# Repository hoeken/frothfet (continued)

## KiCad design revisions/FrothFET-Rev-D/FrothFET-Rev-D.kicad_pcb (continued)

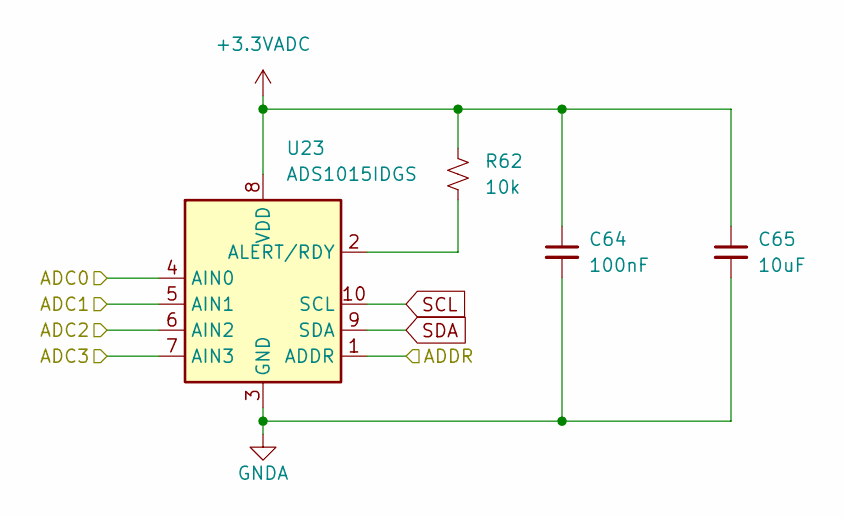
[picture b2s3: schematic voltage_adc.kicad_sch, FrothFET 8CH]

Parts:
C64: 100nF; C_0805_2012Metric_Pad1.18x1.45mm_HandSolder; LCSC C49678
C65: 10uF; C_0805_2012Metric_Pad1.18x1.45mm_HandSolder; LCSC C1952580
R62: 10k; R_0805_2012Metric_Pad1.20x1.40mm_HandSolder; LCSC C84376
U23: ADS1015IDGS; TSSOP-10_3x3mm_P0.5mm; LCSC C193969

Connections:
+3.3VADC: C64.1, C65.1, R62.2, U23.8 (VDD); also elsewhere on the board
GND: C64.2, C65.2, U23.1 (ADDR), U23.3 (GND); also elsewhere on the board
unnamed: R62.1, U23.2 (ALERT/RDY)
SCL: U23.10 (SCL); also elsewhere on the board
SDA: U23.9 (SDA); also elsewhere on the board
VOLT5: U23.4 (AIN0); also elsewhere on the board
VOLT6: U23.5 (AIN1); also elsewhere on the board
VOLT7: U23.6 (AIN2); also elsewhere on the board
VOLT8: U23.7 (AIN3); also elsewhere on the board

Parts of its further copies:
C62: 100nF; C_0805_2012Metric_Pad1.18x1.45mm_HandSolder; LCSC C49678
C63: 10uF; C_0805_2012Metric_Pad1.18x1.45mm_HandSolder; LCSC C1952580
R61: 10k; R_0805_2012Metric_Pad1.20x1.40mm_HandSolder; LCSC C84376
U22: ADS1015IDGS; TSSOP-10_3x3mm_P0.5mm; LCSC C193969

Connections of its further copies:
+3.3VADC: C62.1, C63.1, R61.2, U22.1 (ADDR), U22.8 (VDD); also elsewhere on the board
GND: C62.2, C63.2, U22.3 (GND); also elsewhere on the board
unnamed: R61.1, U22.2 (ALERT/RDY)
SCL: U22.10 (SCL); also elsewhere on the board
SDA: U22.9 (SDA); also elsewhere on the board
VOLT1: U22.4 (AIN0); also elsewhere on the board
VOLT2: U22.5 (AIN1); also elsewhere on the board
VOLT3: U22.6 (AIN2); also elsewhere on the board
VOLT4: U22.7 (AIN3); also elsewhere on the board

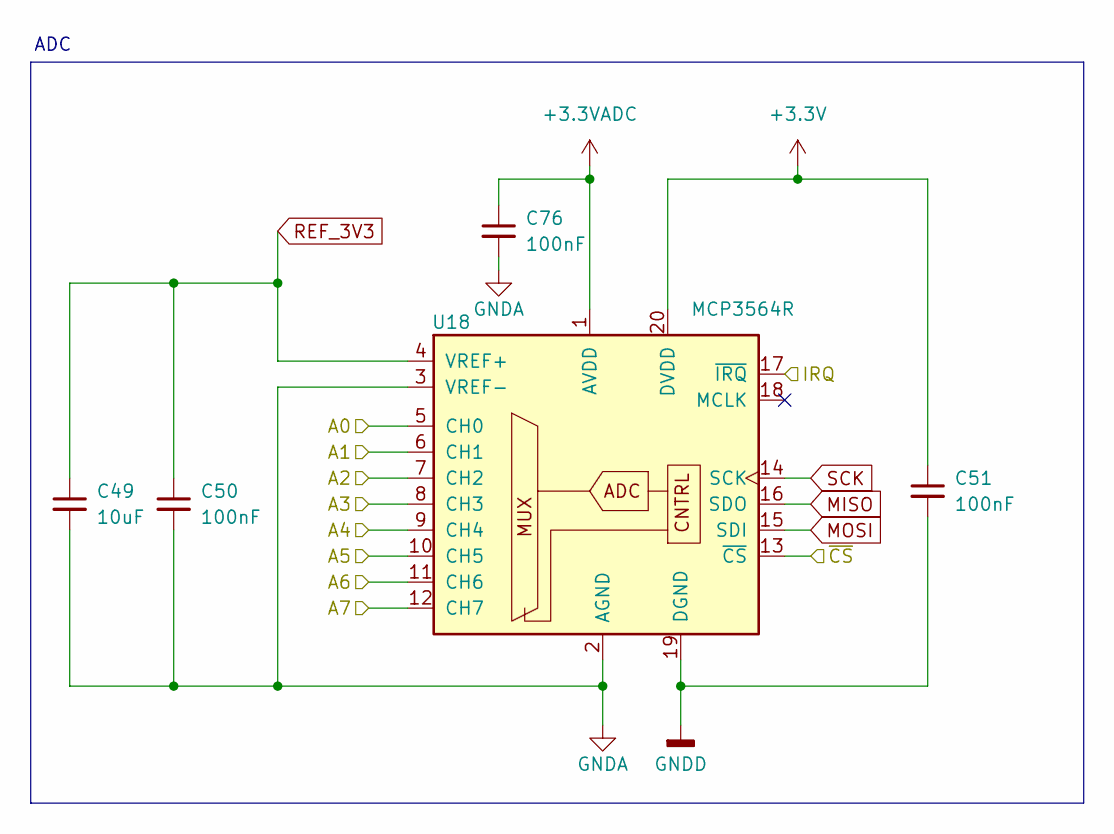
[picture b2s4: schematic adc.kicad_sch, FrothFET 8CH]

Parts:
C49: 10uF; C_0805_2012Metric_Pad1.18x1.45mm_HandSolder; LCSC C1952580
C50, C51, C76: 100nF; C_0805_2012Metric_Pad1.18x1.45mm_HandSolder; LCSC C49678
U18: MCP3564R; TSSOP-20_4.4x6.5mm_P0.65mm; Mouser 579-MCP3564R-E/ST

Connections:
+3.3V: C51.1, U18.20 (DVDD); also elsewhere on the board
+3.3VADC: C76.1, U18.1 (AVDD); also elsewhere on the board
/CHANNEL 1/CURRENT_ADC: U18.5 (CH0); also elsewhere on the board
/CHANNEL 2/CURRENT_ADC: U18.6 (CH1); also elsewhere on the board
/CHANNEL 3/CURRENT_ADC: U18.7 (CH2); also elsewhere on the board
/CHANNEL 4/CURRENT_ADC: U18.8 (CH3); also elsewhere on the board
/CHANNEL 5/CURRENT_ADC: U18.9 (CH4); also elsewhere on the board
/CHANNEL 6/CURRENT_ADC: U18.10 (CH5); also elsewhere on the board
/CHANNEL 7/CURRENT_ADC: U18.11 (CH6); also elsewhere on the board
/CHANNEL 8/CURRENT_ADC: U18.12 (CH7); also elsewhere on the board
/HIRES ADC1/IRQ: U18.17 (~IRQ); also elsewhere on the board
ADC1_CS: U18.13 (~CS); also elsewhere on the board
GND: C49.2, C50.2, C51.2, C76.2, U18.2 (AGND), U18.3 (VREF-), U18.19 (DGND); also elsewhere on the board
MISO: U18.16 (SDO); also elsewhere on the board
MOSI: U18.15 (SDI); also elsewhere on the board
REF_3V3: C49.1, C50.1, U18.4 (VREF+); also elsewhere on the board
SCK: U18.14 (SCK); also elsewhere on the board

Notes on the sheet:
ADC

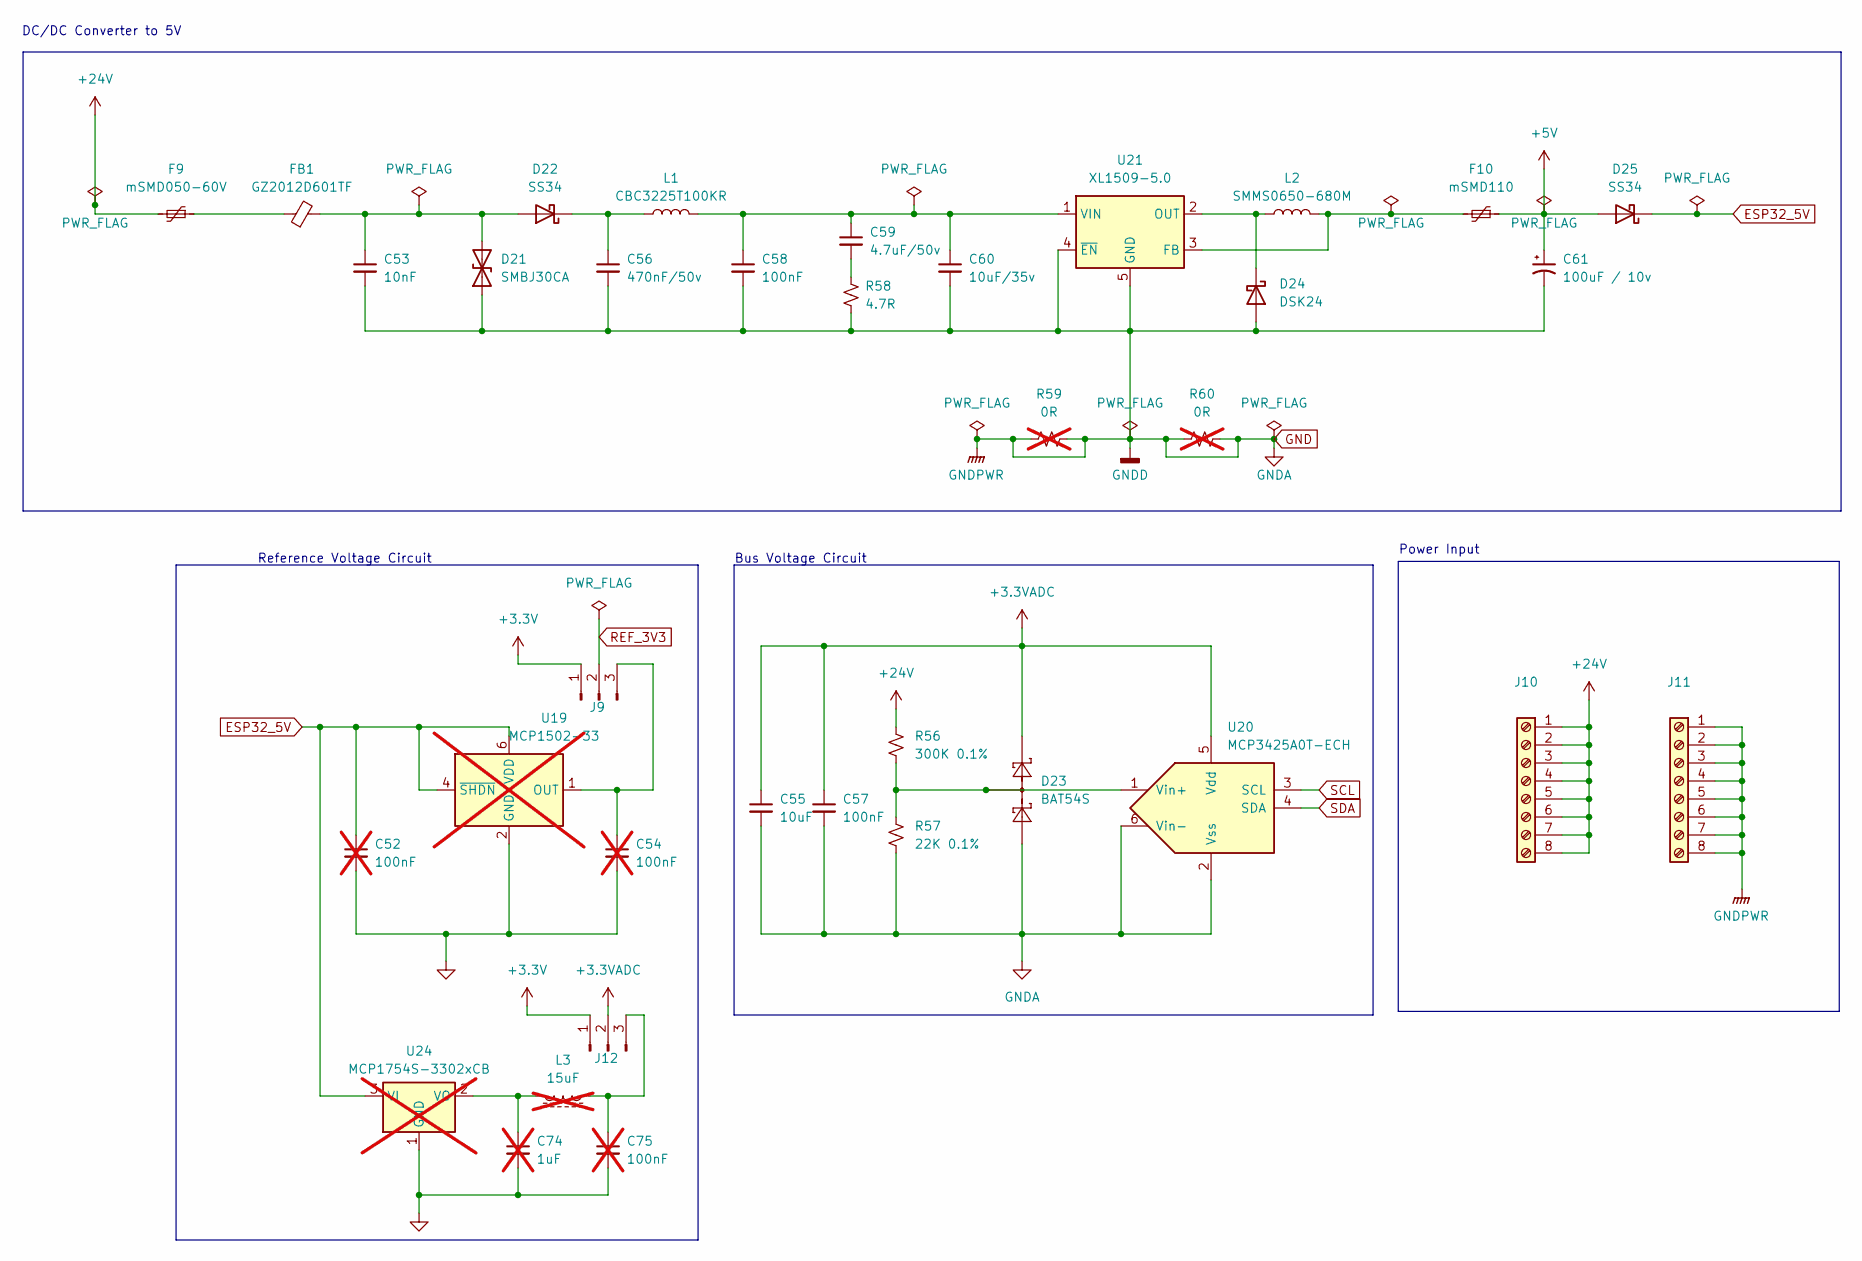
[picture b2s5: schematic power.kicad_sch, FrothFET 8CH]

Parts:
C52, C54, C75: 100nF; C_0805_2012Metric_Pad1.18x1.45mm_HandSolder; LCSC C49678; not fitted
C53: 10nF; C_0805_2012Metric_Pad1.18x1.45mm_HandSolder; LCSC C83170
C55: 10uF; C_0805_2012Metric_Pad1.18x1.45mm_HandSolder; LCSC C1952580
C56: 470nF/50v; C_0805_2012Metric_Pad1.18x1.45mm_HandSolder; LCSC C106843
C57, C58: 100nF; C_0805_2012Metric_Pad1.18x1.45mm_HandSolder; LCSC C49678
C59: 4.7uF/50v; C_0805_2012Metric_Pad1.18x1.45mm_HandSolder; LCSC C2991173
C60: 10uF/35v; C_1206_3216Metric_Pad1.33x1.80mm_HandSolder; LCSC C454102
C61: 100uF / 10v; CP_EIA-3528-21_Kemet-B; LCSC C90975
C74: 1uF; C_0805_2012Metric_Pad1.18x1.45mm_HandSolder; LCSC C519973; not fitted
D21: SMBJ30CA; D_SMB; LCSC C284101
D22, D25: SS34; D_SMA; Mouser 512-SS34
D23: BAT54S; SOT-23; LCSC C727126
D24: DSK24; D_SOD-123; Mouser 610-CMHSH5-2L
F9: mSMD050-60V; Fuse_1812_4532Metric_Pad1.30x3.40mm_HandSolder; LCSC C70113
F10: mSMD110; Fuse_1812_4532Metric_Pad1.30x3.40mm_HandSolder; LCSC C69691
FB1: GZ2012D601TF; L_0805_2012Metric; LCSC C1017
J9, J12: Conn_01x03_Pin; PinHeader_1x03_P2.54mm_Vertical
J10, J11: Screw_Terminal_01x08; Busbar Rev D
L1: CBC3225T100KR; L_1210_3225Metric; LCSC C90321
L2: SMMS0650-680M; L_Chilisin_BMRB00060650; LCSC C2894721
L3: 15uF; L_0805_2012Metric_Pad1.05x1.20mm_HandSolder; Mouser 652-CV201210-150K; not fitted
R56: 300K 0.1%; R_0805_2012Metric_Pad1.20x1.40mm_HandSolder; LCSC C865386
R57: 22K 0.1%; R_0805_2012Metric_Pad1.20x1.40mm_HandSolder; LCSC C865312
R58: 4.7R; R_0805_2012Metric_Pad1.20x1.40mm_HandSolder; LCSC C137513
R59, R60: 0R; R_0805_2012Metric_Pad1.20x1.40mm_HandSolder; not fitted
U19: MCP1502-33; SOT-23-6; Mouser 579-MCP1502T-33E/CHY; not fitted
U20: MCP3425A0T-ECH; SOT-23-6; Mouser 579-MCP3425A0T-E/CH
U21: XL1509-5.0; SOIC-8_3.9x4.9mm_P1.27mm; LCSC C2902368
U24: MCP1754S-3302xCB; SOT-23; Mouser 579-MCP1754ST3302EMB; not fitted

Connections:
+3.3V: J9.1, J12.1; also elsewhere on the board
+3.3VADC: C55.1, C57.1, D23.2 (K), J12.2, U20.5 (Vdd); also elsewhere on the board
+5V: C61.1, D25.2 (A), F10.1; also elsewhere on the board
+24V: F9.2, J10.1, J10.2, J10.3, J10.4, J10.5, J10.6, J10.7, J10.8, R56.2; also elsewhere on the board
ESP32_5V: C52.1, D25.1 (K), U19.4 (~SHDN), U19.6 (VDD), U24.3 (VI); also elsewhere on the board
GND: C52.2, C53.2, C54.2, C55.2, C56.2, C57.2, C58.2, C60.2, C61.2, C74.2, C75.2, D21.1 (A1), D23.1 (A), D24.2 (A), J11.1, J11.2, J11.3, J11.4, J11.5, J11.6, J11.7, J11.8, R57.1, R58.2, R59.1, R59.2, R60.1, R60.2, U19.2 (GND), U19.3 (GND), U19.5 (GND), U20.2 (Vss), U20.6 (Vin-), U21.4 (~EN), U21.5 (GND), U21.6 (GND), U21.7 (GND), U21.8 (GND), U24.1 (GND); also elsewhere on the board
unnamed: C59.2, R58.1
unnamed: C53.1, D21.2 (A2), D22.2 (A), FB1.2
unnamed: C56.1, D22.1 (K), L1.1
unnamed: D23.3 (COM), R56.1, R57.2, U20.1 (Vin+)
unnamed: D24.1 (K), L2.1, U21.2 (OUT)
unnamed: F9.1, FB1.1
unnamed: C54.1, J9.3, U19.1 (OUT)
unnamed: C75.1, J12.3, L3.1
unnamed: F10.2, L2.2, U21.3 (FB)
unnamed: C58.1, C59.1, C60.1, L1.2, U21.1 (VIN)
unnamed: C74.1, L3.2, U24.2 (VO)
REF_3V3: J9.2; also elsewhere on the board
SCL: U20.3 (SCL); also elsewhere on the board
SDA: U20.4 (SDA); also elsewhere on the board

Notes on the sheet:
Reference Voltage Circuit
DC/DC Converter to 5V
Power Input
Bus Voltage Circuit

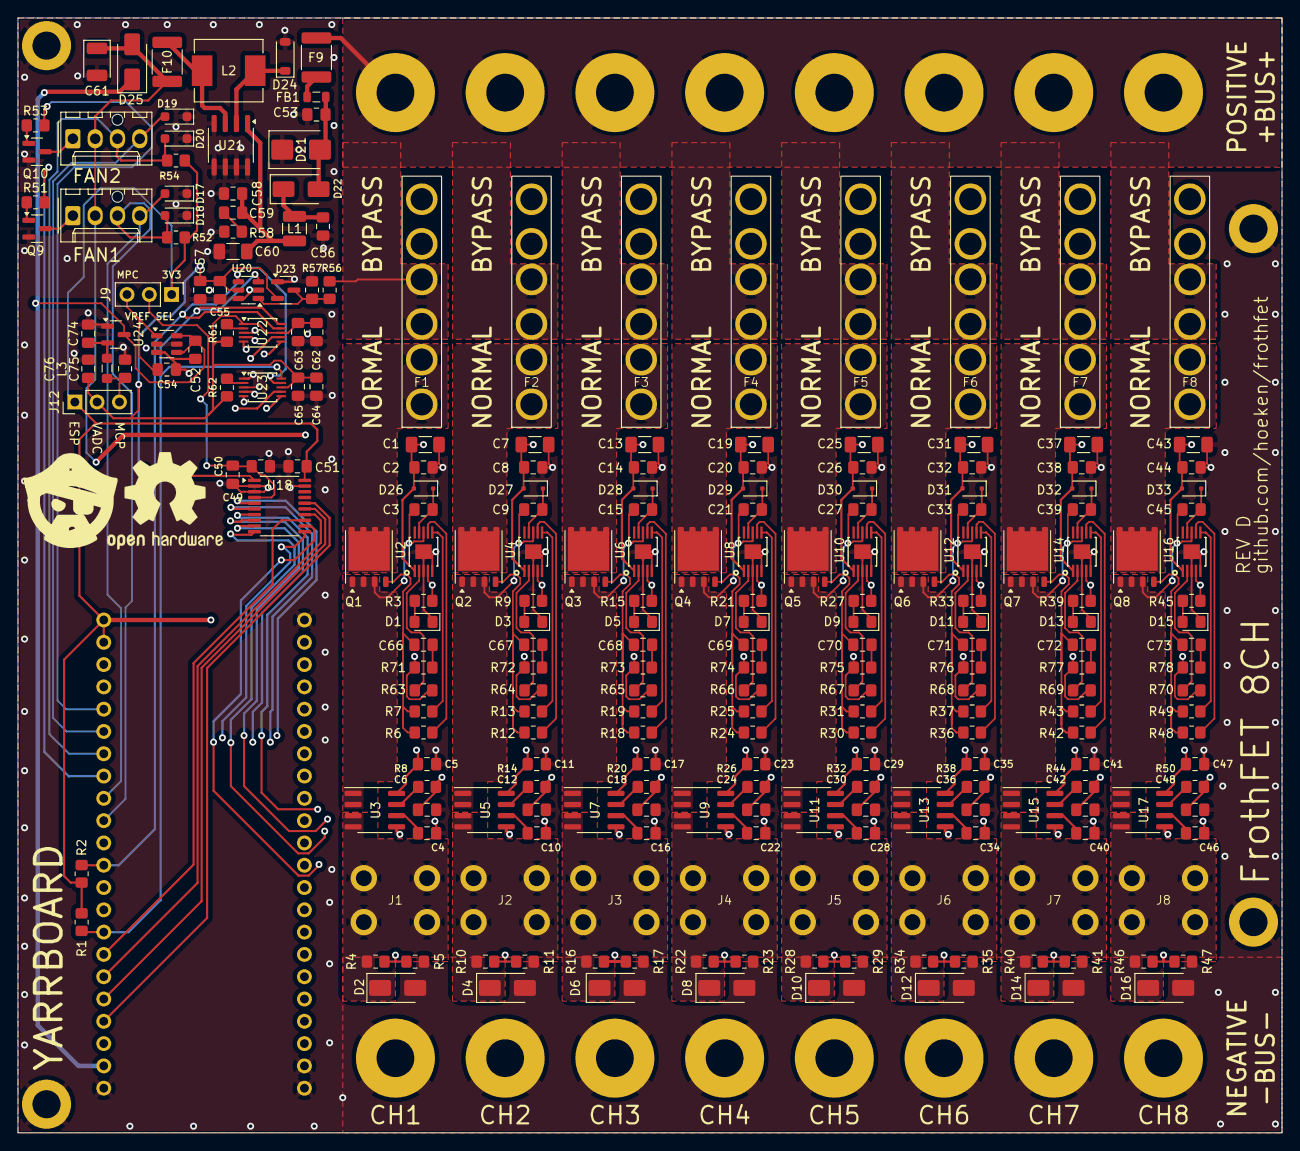
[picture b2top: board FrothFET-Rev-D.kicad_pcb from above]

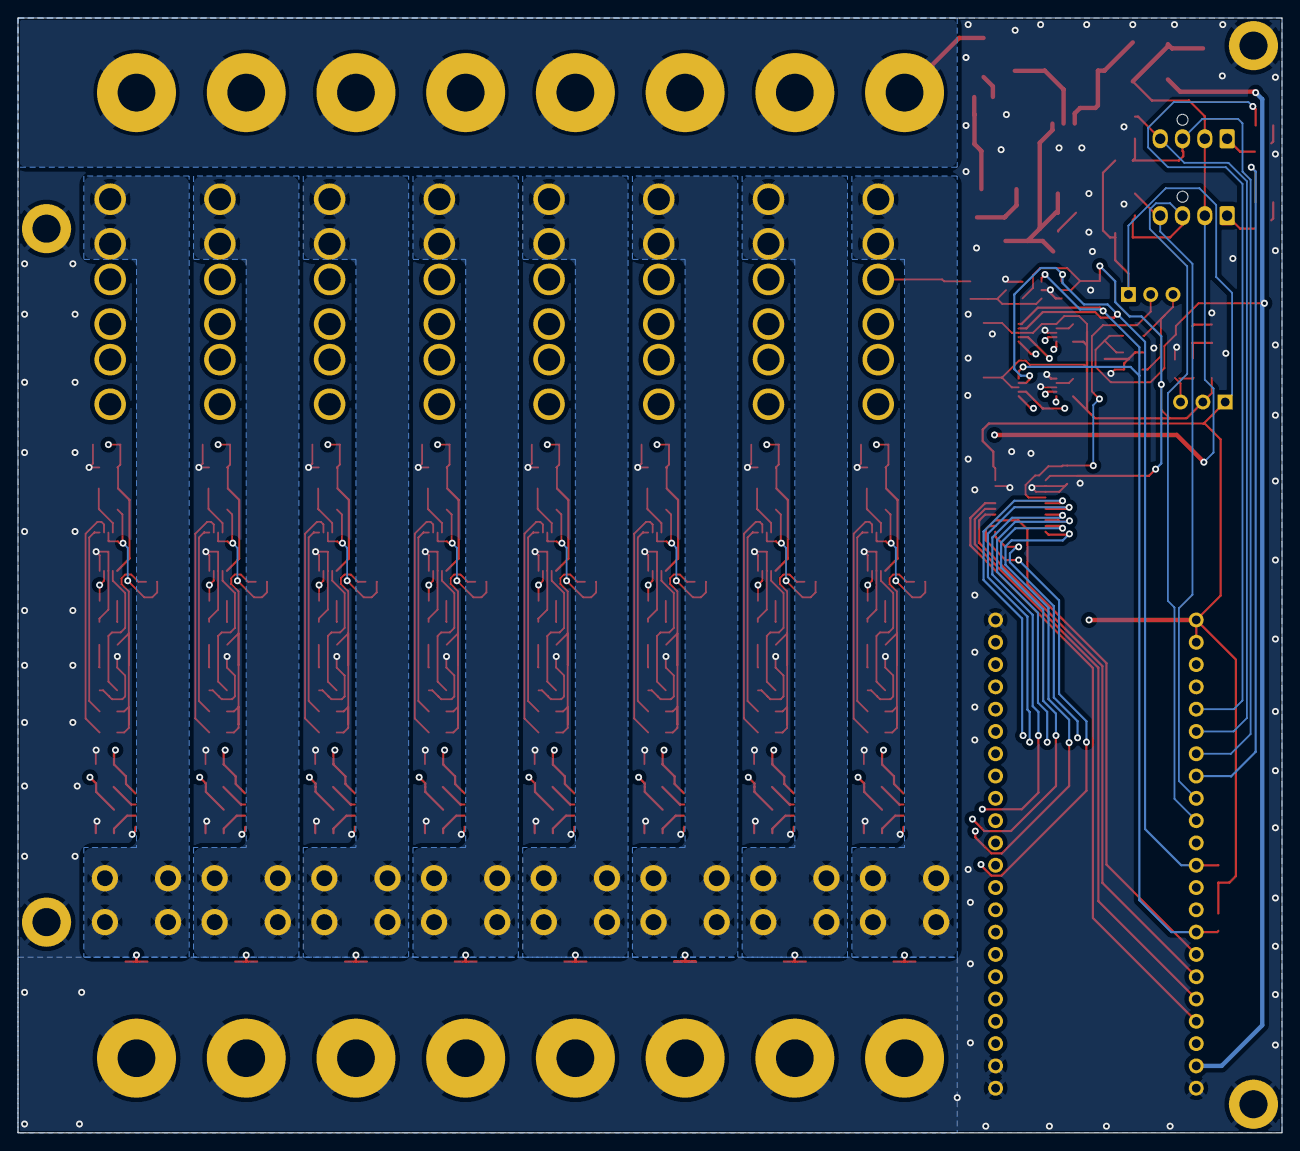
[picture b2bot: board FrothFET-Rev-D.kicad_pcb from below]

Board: 4 copper layers, 144.0 x 127.0 mm, 251 parts (2 on the bottom side), 157 nets.

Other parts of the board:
D17, D18, D19, D20: PESD3V3L1BA; D_SOD-323_HandSoldering
FAN1, FAN2: Fan_4pin; Molex 0470531000
Q9, Q10: 2N7002; SOT-23
R51, R52, R53, R54: 1k; R_0805_2012Metric_Pad1.20x1.40mm_HandSolder

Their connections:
+3.3V: R52.2, R54.2; also elsewhere on the board
+5V: FAN1.2 (+), FAN2.2 (+); also elsewhere on the board
FAN_MOSFET1: R51.2; also elsewhere on the board
FAN_MOSFET2: R53.2; also elsewhere on the board
FAN_PWM1: D17.2 (A2), FAN1.4 (PWM); also elsewhere on the board
FAN_PWM2: D19.2 (A2), FAN2.4 (PWM); also elsewhere on the board
FAN_TACH1: D18.2 (A2), FAN1.3 (Tacho), R52.1; also elsewhere on the board
FAN_TACH2: D20.2 (A2), FAN2.3 (Tacho), R54.1; also elsewhere on the board
GND: D17.1 (A1), D18.1 (A1), D19.1 (A1), D20.1 (A1), Q9.2 (S), Q10.2 (S); also elsewhere on the board
unnamed: FAN1.1 (-), Q9.3 (D)
unnamed: FAN2.1 (-), Q10.3 (D)
unnamed: Q9.1 (G), R51.1
unnamed: Q10.1 (G), R53.1

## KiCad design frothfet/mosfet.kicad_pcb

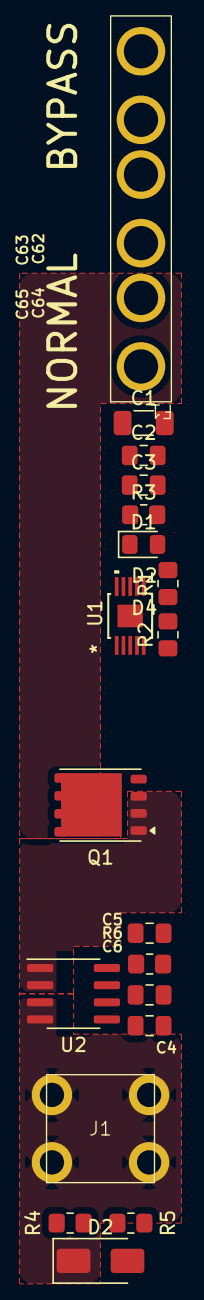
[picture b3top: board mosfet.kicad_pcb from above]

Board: 2 copper layers, 19 parts (0 on the bottom side), 17 nets, no tracks yet.

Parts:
C1: 10uF/35v; C_1206_3216Metric_Pad1.33x1.80mm_HandSolder
C2: 100nF/50v; C_0805_2012Metric_Pad1.18x1.45mm_HandSolder
C3, C5: 100nF; C_0805_2012Metric_Pad1.18x1.45mm_HandSolder
C4: 1nF; C_0805_2012Metric_Pad1.18x1.45mm_HandSolder
C6: 4.7nF; C_0805_2012Metric_Pad1.18x1.45mm_HandSolder
D1: LED; LED_0805_2012Metric_Pad1.15x1.40mm_HandSolder
D2: SS16; D_SMA
F1: ATC Fuse Bypass; ATC Bypass Fuse
J1: Conn_01x01; T44001
Q1: ISC011N06LM5ATMA1; Infineon_PG-TDSON-8_6.15x5.15mm
R1, R6: 1k; R_0805_2012Metric_Pad1.20x1.40mm_HandSolder
R2: 300K 0.1%; R_0805_2012Metric_Pad1.20x1.40mm_HandSolder
R3: 22K 0.1%; R_0805_2012Metric_Pad1.20x1.40mm_HandSolder
R4, R5: 0R; R_0805_2012Metric_Pad1.20x1.40mm_HandSolder
U1: LTC7004EMSE-PBF; MSE_10_ADI
U2: ACS725xLCTR-20AU; ACS7XX

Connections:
+3.3V: C5.1, U2.8 (VCC)
+5V: C1.1, C2.1, U1.1 (VCC)
/CURRENT_ADC: C6.1, R6.1
/PWM: R1.1, U1.4 (INP)
/VOLT_ADC: R2.1, R3.2
GNDA: C4.2, C5.2, C6.2, U2.5 (GND)
GNDPWR: C1.2, C2.2, D1.1 (K), D2.2 (A), R3.1, U1.2 (VCCUV), U1.3 (GND), U1.5 (OVLO), U1.EPAD
unnamed: D1.2 (A), R1.2
unnamed: D2.1 (K), F1.3, J1.1, R2.2, U2.3 (IP-), U2.4 (IP-)
unnamed: F1.1, Q1.1 (D)
unnamed: Q1.2 (G), R4.1, R5.1
unnamed: C3.2, Q1.3 (S), U1.8 (TS), U2.1 (IP+), U2.2 (IP+)
unnamed: C3.1, U1.9 (BST)
unnamed: R5.2, U1.6 (TGDN)
unnamed: R4.2, U1.7 (TGUP)
unnamed: C4.1, U2.6 (FILTER)
unnamed: R6.2, U2.7 (VIOUT)

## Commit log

2024-08-16 added kicad files.
2024-08-16 Update README.md
    better readme
2024-08-16 Update README.md
    psu
2024-08-16 added todo
2024-08-16 schematic looking clean.
2024-08-16 todo
2024-08-17 updated bom
2024-08-17 just need to route it...
2024-08-17 starting the mega route.
2024-08-17 fully routed
2024-08-17 clean drc
2024-08-17 erc clean
2024-08-17 just silkscreen and final review left.
2024-08-17 changed senders to screw terminals
2024-08-17 added busbar 3d model and more routing.
2024-08-17 3d model.
2024-08-17 fixed busbar resize.
2024-08-17 better esp32-s3 3d model.
2024-08-17 more 3d models.
2024-08-17 added atc fuses.
2024-08-18 more pre-production tweaks
2024-08-18 todo update
2024-08-19 added mosfet thermistor
2024-08-21 lots of big updates
2024-08-21 changed to MIC5014
2024-08-26 first pass at ltc7004
2024-10-02 renamed to frothfet.
2024-10-02 prep for new HierarchialPCB test
2024-10-02 Revert "prep for new HierarchialPCB test"
    This reverts commit 7ba467f7ba771a9ed3b62c58bdcef6315b0965ad.
2024-10-02 back to a good state
2024-10-02 first pass at new subcircuit layout
2024-10-02 resized pcb
2024-10-03 drc passing
2024-10-03 fatter power trace and layer 3 is fully ground plane now.
2024-10-04 reannotate
2024-10-04 updated a couple components, flyback diode.
2024-10-05 added selector for 3.3VADC and finalized board.
2024-10-05 Update README.md
    updated readme
2024-10-06 wrong led pn
2024-10-23 updated dnp, updatd channel voltage divider, added discharge mosfet circuit
2024-10-25 todo list and rev d testing
2024-10-25 updated voltage divider values
2024-10-25 added power leds
2024-10-25 updated the adc voltage regulator.
2024-10-25 added hole to screw connector
2024-10-25 added extra adc control lines
2024-10-25 fans are now simple on/off, cleaned up power supply drawings
2024-10-26 updated fans and also new "dump" mosfet circuit
2024-10-26 added config.
2024-10-26 added piezo buzzer
2024-10-26 updated adc and adc power supply schematics.
2024-10-29 updated todo for eventual Rev E
2024-10-29 added the up to date rev d schematic
2024-10-30 tweaks to rev d
2024-10-30 rev e channel changes.
2024-10-30 consolidated on a single adc
2024-10-31 updated the dummy load schematic.
2024-11-01 removed uvlo resistor, tied to gnd.
2024-11-01 updated todo for rev e
2024-11-01 updated pins: channel rgbs + channel 5+6 pwm pins
2024-11-01 changed to jumper resistor for voltage selection.
2024-11-01 re-calculate channel voltage divider <= 30k and 3.3v output
2024-11-01 recalculate values for adc filters - 1khz should be fine
2024-11-02 started work on rev e, looking clean at 13mm
2024-11-02 more progress on the next rev.
2024-11-02 layout of the mosfet channel passives looking good.
2024-11-02 progress - new channel layout good, zones + edges + holes fixed.
2024-11-02 changed to 0603 and various tweaks
2024-11-02 24v to fuse now on both sides.
2025-07-31 updated to kicad v9
2025-07-31 updated todo.
2025-08-15 started the process of re-layout
2025-08-16 almost ready for routing.
2025-09-10 added new esp32-s3 template and switched to lm74502 mosfet driver.
2025-09-11 updated calculations, updated esp32-s3 schematic, updated layout.
2025-09-12 worked on 3d models for all parts.
2025-09-13 worked on the bom and footprint placement
2025-09-27 changed the adc voltage regulator and vref to more common parts.
2025-09-28 lots of work on the analog system
2025-09-30 moved back to a single ground plane
2025-10-01 cant remember
2025-10-02 imported latest esp32-s3 module
2025-10-02 piezo resistor
2025-10-04 about 50% routed
2025-10-04 finished re-routing the board.
2025-10-04 silkscreen done, erc+drc passing
2025-10-04 via stitching done.
2025-10-04 bom and placement all check out. ready for production!
2025-10-05 rounded board edges
2025-10-06 updated busbar design and added button silkscreen
2025-10-07 send the board for production
2025-10-08 tidy up for Rev E release
2025-11-06 updated todo for Rev F design
2025-12-03 pulled in updated esp32-s3 schematic
2025-12-03 removed adc and adc vref
2025-12-03 removed unneccesary bleed circuit
2025-12-03 switched to ina226 for voltage and current measurement
2025-12-03 added lm75b temperature sensor to channels.
2025-12-03 wired the i2c addresses.
2025-12-03 added the buffer circuit
2025-12-03 added ideal diode to 5v
2025-12-03 added bulk capacitor on 24v
2025-12-03 power supply tweaks and tidy
2025-12-04 changed to a single ground
2025-12-04 added test points
2025-12-04 worked on routing load channel.
2025-12-04 this is gonna be a beast to route
2025-12-05 ready for multi channel work
2025-12-05 channel zones are looking good.
2025-12-05 channel routing is looking good.
2025-12-05 double checked i2c capacitance
2025-12-05 channel routing is basically done
2025-12-05 starting to layout the rest of the components.
2025-12-06 mostly routed
2025-12-06 added via stitching
2025-12-06 drc errors fixed.
2025-12-06 silkscreen and 3d models complete
2025-12-06 added some lcsc part numbers
2025-12-06 caught a bug with pulldown instead of pullup on LM74502H
2025-12-07 added more esd protection to 3.3v and 5v rails.
2025-12-07 added support for ALERT pin from INA226 for overcurrent protection (hopefully)
2025-12-07 rearranged the buttons
2025-12-07 rearranged leds and cleaned things up a bit.
2025-12-07 working on bom
2025-12-07 changed to XFCN 508 because 507 wasnt available on jlc
2025-12-08 re-routed everything again
2025-12-08 tidied up the power schematic a little bit.
2025-12-08 fixed a minor zone spacing issue
2025-12-08 updated todo
2025-12-08 swapped piezo and output enable due to power on glitch on gpio14
2025-12-08 changed buffer to 74LVC541A
2025-12-08 notes on gate driver
2025-12-12 add esd protection to each channel output
2025-12-12 placement and routing plan for channels is fixed.
2025-12-12 fully routed and passing drc again
2025-12-12 small schematic cleanup
2025-12-12 pulled in latest version of esp32 schematic
2025-12-12 going to stick with the xl1509 as its working just fine.
2025-12-12 updated datasheets
2025-12-12 switched to bav199 on bus voltage
2025-12-12 added via stitching back in
2025-12-13 updated bom and checked placement
2026-01-09 updated esp32-s3 schematic
2026-01-09 update 24v to 5v power supply with brineomatic one
2026-01-10 finished routing the board.
2026-01-10 finished vias, added a bunch of test points
2026-01-10 silkscreen done
2026-01-10 bom and placement looking good.
2026-01-10 switch back to T507 fuse holder is complete
2026-01-10 a few routing tweaks, removed DNP on pin headers for uart0
2026-01-12 added fuse p/n and drawing
2026-01-15 final bom tweaks for manufacturing
2026-01-15 added CHANGELOG.md
2026-04-01 apparently i never committed the changelog!
2026-04-01 added the Rev F case
2026-04-13 added spreadsheet
2026-04-14 stubbed the frothfet readme.
2026-04-14 added Rev F schematic
2026-04-16 renamed bus bar source
2026-05-05 updated with plans for a frothfet mini board.
